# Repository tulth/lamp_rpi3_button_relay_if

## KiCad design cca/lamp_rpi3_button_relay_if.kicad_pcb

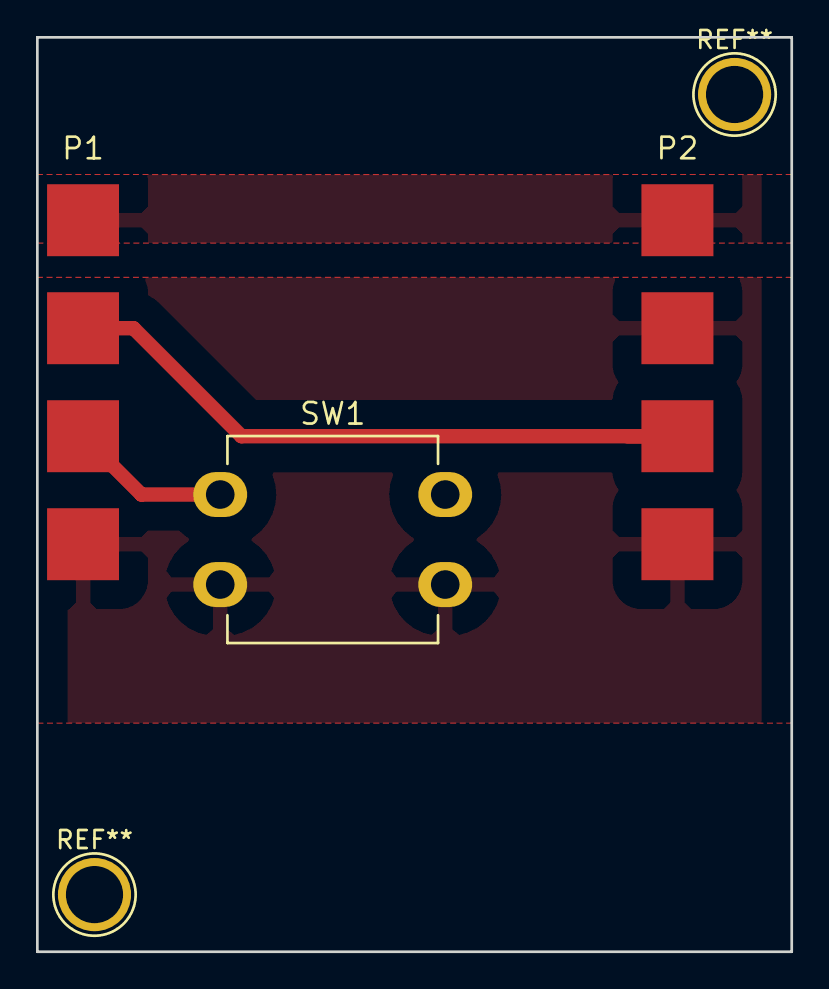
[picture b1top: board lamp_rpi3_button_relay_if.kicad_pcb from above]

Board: 2 copper layers, 41.9 x 50.8 mm, 3 parts (0 on the bottom side), 4 nets.

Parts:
P1: lamp_cca_rpi3_conn; conn_4_big_pads
P2: lamp_cca_relay_conn; conn_4_big_pads
SW1: TSA12110

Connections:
+5V: P1.1, P2.1
GND: P1.4, P2.2, P2.4, SW1.3, SW1.4
unnamed: P1.2, P2.3
unnamed: P1.3, SW1.1

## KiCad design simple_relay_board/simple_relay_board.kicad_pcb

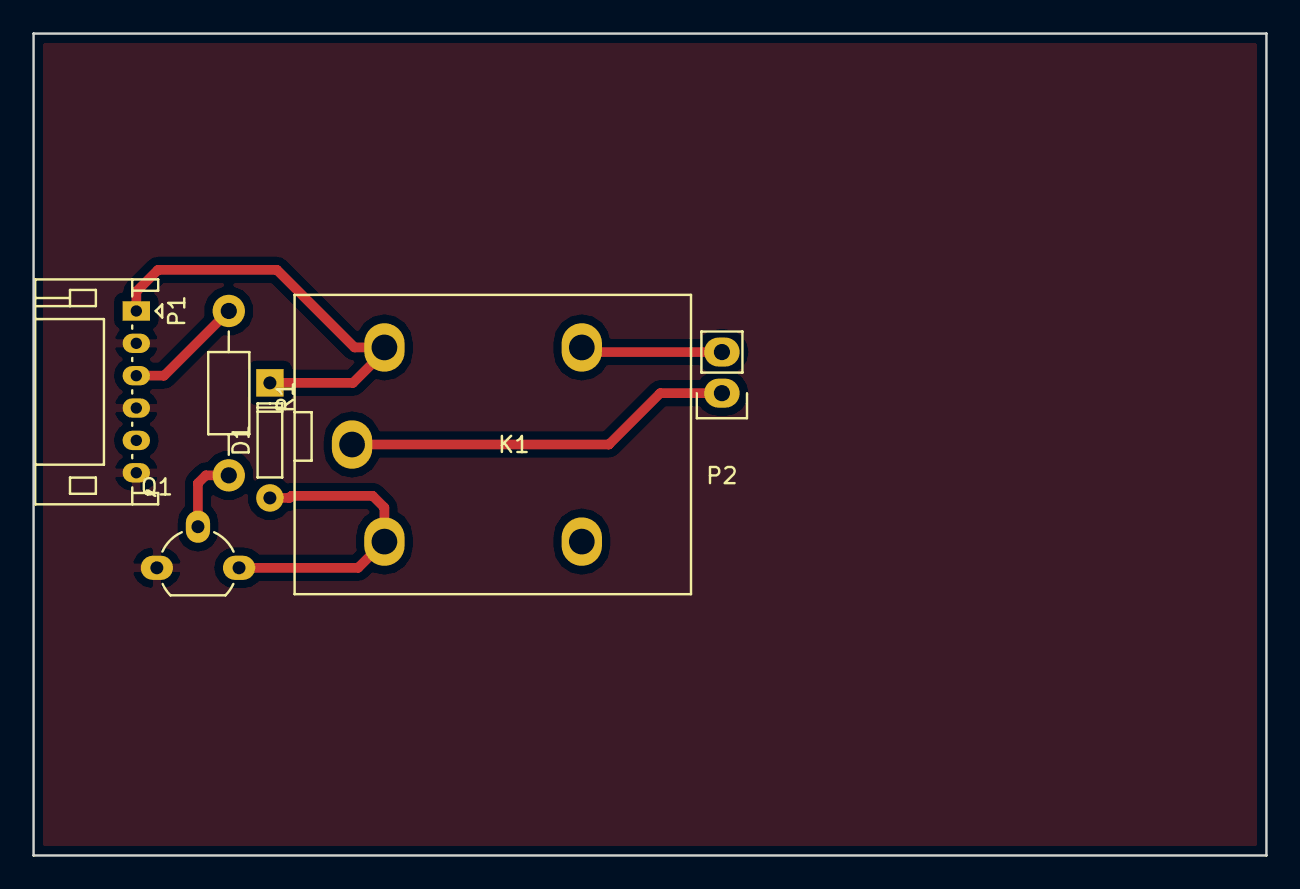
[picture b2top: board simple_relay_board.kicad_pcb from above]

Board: 2 copper layers, 76.2 x 50.8 mm, 6 parts (0 on the bottom side), 7 nets.

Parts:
D1: 1N4148; DO-35
K1: G5LE-14_DC5; RELAY_1_FORM_C
P1: tstat_ui_conn; JST_PH_RIGHT_6pin
P2: CONN_01X02; Pin_Header_Straight_1x02
Q1: 2N3904; TO-92_Molded_Wide_Oval
R1: 4.75K; Resistor_Horizontal_RM10mm

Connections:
+5V: D1.1, K1.2, P1.1
GND: P1.2, P1.4, P1.6, Q1.1
unnamed: D1.2, K1.5, Q1.3
unnamed: K1.1, P2.1
unnamed: K1.3, P2.2
unnamed: P1.3, R1.1
unnamed: Q1.2, R1.2

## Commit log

2016-09-10 Initial commit. needs better board outline and mounting holes
2016-09-10 rm generated trash files
2016-09-10 First cut for simple relay board...about to try flatcamming it
2016-09-16 minor cca updates
2016-09-16 Add lamp control mqtt code and service
2016-09-16 fix publish
